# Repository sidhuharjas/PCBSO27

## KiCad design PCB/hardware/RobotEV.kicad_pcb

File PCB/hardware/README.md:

# EV Controller Board — Rev D (100% Through-Hole, Zero SMD)

Custom 2-layer carrier PCB for a **Science Olympiad Electric Vehicle (Division C, 2027)** built around a **Raspberry Pi Pico 2 (RP2350)**, an **8xAA battery pack**, a **Weka dual 20 A brushed ESC**, **two AS5600 magnetic wheel encoders**, a **WitMotion WT901 UART IMU**, and a **Waveshare 1.69" ST7789V2 IPS LCD**.

**Board geometry:** `85 × 65 mm`, 4 mm rounded corners, 4× M3 mounting holes on a `77 × 57 mm` pattern (100% drop-in chassis-compatible with Rev B/C).

---

## What Changed in Rev D (vs. Rev C)

| Metric / Feature | Rev C | **Rev D** | Improvement |
|---|---|---|---|
| **Soldered SMD components** | **26** | **0** | **100% through-hole — standard iron only** |
| **Electrical components to solder** | 29 | **12** | **59% fewer electrical parts** |
| **Total soldered parts (incl. connectors)** | 40 | **23** | **43% fewer solder joints** |
| **XT30 polarity (`J1` / `J2`)** | Reversed (`+` on GND!) | **Fixed (`Pin 1 = -`, `Pin 2 = +`)** | **Prevented dead short on plug-in** |
| **15 A main fuse (`F1`)** | Soldered 2920 SMD | **Keystone 3568 mini blade holder** | **Tool-free 2-second competition swap** |
| **15 A power bus copper** | Single-sided 3.0 mm | **Double-sided 3.0 mm (`F.Cu + B.Cu`)** | **2× copper cross-section (6 mm eff.)** |
| **3.3 V rail regulator** | External `AMS1117-3.3` + MLCC | **Pico 2 onboard `RT6154A` SMPS** | **Zero oscillation risk + USB-only bench testing** |
| **Hold-up cap `C14` rating** | 470 µF 16 V | **470 µF 25 V** | **Proper derating for 13.2 V fresh 8×AA** |
| **Routed signal/power vias** | 8 | **1** (0 on signals!) | **Cleaner 2-layer routing + solid GND planes** |

### Critical Bug Fixed from Rev C
- **Reversed XT30 polarity on `J1` and `J2`:** Official KiCad `AMASS_XT30PW-M` and `AMASS_XT30PW-F` footprints map **Pin 1 (square pad, `-` silk)** to negative and **Pin 2 (round pad, `+` silk)** to positive. Rev C wired Pin 1 to `VBAT`/`VBAT_F` and Pin 2 to `GND`, which would have dead-shorted the battery pack through `D4` and blown the fuse (or damaged the ESC) on first connection. Rev D corrects both connectors to `Pin 1 = GND (-)`, `Pin 2 = VBAT / VBAT_F (+)`, which also places `J1 (+)` and `J2 (+)` directly facing each other (`9.85 mm` apart) right beside the Keystone 3568 blade fuse holder (`9.92 mm` pitch).

### 17 Eliminated Components (Why Every Removal Makes the Board Better)
1. **`U3` (`AMS1117-3.3`) + `C13` + `C3` removed:** The Pico 2's built-in RT6154A buck-boost regulator (`Pin 36: 3V3`) is rated for **300 mA** external load. Total worst-case 3.3 V draw on this board is **≤128 mA** (LCD ≤90 mA + 2× AS5600 ~13 mA + WT901 <25 mA — >2.3× safety margin). Removing `U3` eliminates AMS1117's notorious low-ESR MLCC oscillation risk, eliminates back-powering hazards when plugged into USB, and lets you bench-test **the LCD, IMU, and encoders over USB alone without a battery**.
2. **`J6` (WT901 IMU) moved from `+5V` to `+3V3`:** The WT901 datasheet specifies `3.3–5 V` supply (`<25 mA`, `11.5 mA` typ.) and 3.3 V-only UART I/O. Running it on `+3V3` guarantees its UART stays powered in sync with the RP2350 on both battery and USB.
3. **`C12` (100 µF) removed:** Redundant with `C2` (`10 µF` low-ESR ceramic) and the Pico 2's onboard `47 µF` `VSYS` capacitor; keeps capacitive load well within RECOM `R-78E5.0-0.5`'s `≤100 µF` output-cap limit.
4. **`C5`, `C6`, `C7`, `C8` removed (kept shared `C4` 100 nF on east `+3V3` bus):** All four off-board breakouts (LCD, WT901, 2× AS5600) already carry their own onboard decoupling capacitors.
5. **`R3` (1 kΩ) removed:** The `100 kΩ / 22 kΩ` divider (`R1 || R2 = 18 kΩ`) already limits fault current into `GP26/ADC0` to `<0.2 mA` and forms an `88 Hz` low-pass filter directly with `C11` (`100 nF`).
6. **`R4`, `R5`, `C9`, `C10` removed:** The RP2350 has built-in programmable pull-ups (~50–80 kΩ) on `GP15`/`GP16` and handles button debounce in 5 lines of firmware.
7. **`D1`, `R6`, `D2`, `R7` removed:** Use the Pico 2's onboard `GP25` LED, the 1.69" IPS LCD, and test pads `TP1`–`TP4` for status and power verification (also frees `GP17` for future expansion).

---

## Power Architecture

```text
8xAA Pack (9.6–13.2 V)
  │
  ▼  J1 (XT30PW-M: Pin 1 '-' GND, Pin 2 '+' VBAT)
  ├──[ 3.0 mm F.Cu + 3.0 mm B.Cu bus ]──► F1 (Keystone 3568 + 15 A Mini Blade Fuse)
  │                                         │ VBAT_F
  │                                         ├──[ 3.0 mm F.Cu + 3.0 mm B.Cu ]──► J2 (XT30PW-F -> Weka Dual 20A ESC)
  │                                         ├──► D4 (P6KE18A 600 W TVS -> GND, clamps brushed-motor spikes)
  │                                         └──► J3 (Logic Power Switch, <250 mA)
  │                                                │ VBAT_SW (TP4)
  │                                                ▼
  │                                              D3 (1N5822 40V 3A Schottky: reverse-polarity + hold-up isolator)
  │                                                │ VBAT_D
  │                                                ├──► C14 (470 µF 25V hold-up) + C1 (10 µF 50V ceramic)
  │                                                ├──► R1 (100k) / R2 (22k) + C11 (100nF) ──► Pico GP26/ADC0
  │                                                └──► U2 (RECOM R-78E5.0-0.5, 5 V 500 mA buck)
  │                                                       │ +5V (TP1) + C2 (10 µF 50V ceramic)
  │                                                       ▼
  │                                                     D5 (1N5822 40V 3A Schottky OR-ing diode)
  │                                                       │ VSYS
  │                                                       ▼
  │                                              U1 (Raspberry Pi Pico 2, Pin 39 VSYS — USB-safe!)
  │                                                       │ Pin 36: +3V3 (onboard RT6154A SMPS, 300 mA max)
  │                                                       └──► C4 (100nF), TP2, J4 (ENC_L), J5 (ENC_R), J6 (WT901), J7 (LCD)
```

### Battery Voltage Sense Math (`GP26 / ADC0`)
- Divider ratio: `V_ADC = VBAT_D × 22k / (100k + 22k) = VBAT_D × 0.18033`
- Account for ~0.30 V drop across `D3` (`1N5822` at ~150 mA):
  `V_BATT ≈ (V_ADC / 0.18033) + 0.30 V`
- Fresh 8×AA alkaline (`13.2 V` → `VBAT_D ≈ 12.9 V`): `V_ADC = 2.33 V` (safe margin below `3.3 V` ADC max; survives up to `18.6 V` input!).

---

## RP2350 Pin Map (`U1` — Raspberry Pi Pico 2)

| Pico Pin | GPIO | Net | Destination | Firmware Notes |
|---|---|---|---|---|
| 1 | GP0 | `IMU_TX` | `J6.2` (WT901 RX) | UART0 TX (3.3 V logic) |
| 2 | GP1 | `IMU_RX` | `J6.3` (WT901 TX) | UART0 RX (3.3 V logic) |
| 4 | GP2 | `ESC_L` | `J10.1` | 50 Hz servo PWM (left motor) |
| 5 | GP3 | `ESC_R` | `J10.2` | 50 Hz servo PWM (right motor) |
| 6 | GP4 | `ENC_L_SDA` | `J4.3` | I2C0 SDA (AS5600 `0x36`, breakout has 4.7k pull-up) |
| 7 | GP5 | `ENC_L_SCL` | `J4.4` | I2C0 SCL |
| 9 | GP6 | `ENC_R_SDA` | `J5.3` | I2C1 SDA (AS5600 `0x36`, breakout has 4.7k pull-up) |
| 10 | GP7 | `ENC_R_SCL` | `J5.4` | I2C1 SCL |
| 12 | GP9 | `LCD_CS` | `J7.5` | SPI1 CS |
| 14 | GP10 | `LCD_SCK` | `J7.4` | SPI1 SCK |
| 15 | GP11 | `LCD_MOSI` | `J7.3` | SPI1 TX |
| 16 | GP12 | `LCD_DC` | `J7.6` | LCD Data/Command |
| 17 | GP13 | `LCD_RST` | `J7.7` | LCD Reset |
| 19 | GP14 | `LCD_BL` | `J7.8` | LCD Backlight (PWM dimmable) |
| 20 | GP15 | `BTN_START` | `J8.1` | **Enable internal pull-up** + 20 ms software debounce |
| 21 | GP16 | `BTN_MODE` | `J9.1` | **Enable internal pull-up** + 20 ms software debounce |
| 22 | GP17 | *(spare)* | — | Freed in Rev D (use Pico onboard `GP25` LED for status) |
| 31 | GP26 | `VBAT_ADC` | `R1`/`R2`/`C11` | ADC0 battery monitor (`88 Hz` LPF) |
| 36 | 3V3 | `+3V3` | `J4, J5, J6, J7, C4, TP2` | Onboard RT6154A SMPS output (≤128 mA / 300 mA max) |
| 39 | VSYS | `VSYS` | `D5.1 (K)` | OR-ed 5 V rail (~4.7 V after D5; USB-safe) |
| 3,8,13,18,23,28,33,38 | GND | `GND` | Solid top + bottom pours | Connected to 85 stitching vias |

---

## Connector Pinouts (Pin 1 = Square Pad on PCB)

| Ref | Label | Connector | Pinout |
|---|---|---|---|
| `J1` | `BATT 8xAA` | `AMASS XT30PW-M` | `1 = GND (-)` · `2 = VBAT (+)` |
| `J2` | `ESC PWR` | `AMASS XT30PW-F` | `1 = GND (-)` · `2 = VBAT_F (+)` |
| `J3` | `PWR SW` | `1×2 2.54 mm` header | `1 = VBAT_F` · `2 = VBAT_SW` |
| `J4` | `ENC L` | `JST-PH 4-pin` (2.0 mm) | `1 = +3V3` · `2 = GND` · `3 = SDA (GP4)` · `4 = SCL (GP5)` |
| `J5` | `ENC R` | `JST-PH 4-pin` (2.0 mm) | `1 = +3V3` · `2 = GND` · `3 = SDA (GP6)` · `4 = SCL (GP7)` |
| `J6` | `WT901` | `JST-PH 4-pin` (2.0 mm) | `1 = +3V3` · `2 = IMU_TX (→WT901 RX)` · `3 = IMU_RX (←WT901 TX)` · `4 = GND` |
| `J7` | `LCD` | `2×4 2.54 mm` header | Odd: `1=+3V3, 3=MOSI, 5=CS, 7=RST` · Even: `2=GND, 4=SCK, 6=DC, 8=BL` |
| `J8` | `START` | `JST-XH 2-pin` (2.5 mm) | `1 = BTN_START (GP15)` · `2 = GND` |
| `J9` | `MODE` | `JST-XH 2-pin` (2.5 mm) | `1 = BTN_MODE (GP16)` · `2 = GND` |
| `J10` | `ESC SIG` | `1×3 2.54 mm` header | `1 = ESC_L (GP2)` · `2 = ESC_R (GP3)` · `3 = GND` *(do NOT connect ESC BEC +5V)* |

---

## Complete PCB BOM (100% Through-Hole — 0 SMD, 23 Soldered Parts)

See `hardware/BOM.xlsx` for clickable vendor/cost rollups and off-board parts.

### 12 Electrical Components (9 Unique Part Types)
| Ref(s) | Qty | Value | Package / Footprint | Example Part Number |
|---|---|---|---|---|
| `F1` | 1 | 15 A Mini Blade | `Fuseholder_Blade_Mini_Keystone_3568` | Keystone `3568` + Littelfuse `0297015.WXNV` |
| `D4` | 1 | `P6KE18A` TVS | `D_DO-15_P10.16mm_Horizontal` | Littelfuse `P6KE18A` |
| `D3, D5` | 2 | `1N5822` 40V 3A | `D_DO-201AD_P12.70mm_Horizontal` | ON Semi / Vishay `1N5822` |
| `C14` | 1 | `470 µF 25 V` | `CP_Radial_D8.0mm_P3.50mm` | Nichicon `UPW1E471MPD` |
| `C1, C2` | 2 | `10 µF 50 V` X7R/S | `C_Disc_D6.0mm_W4.4mm_P5.00mm` | TDK `FG20X7R1H106KRT00` / Murata `RDEC71H106K3K1H03B` |
| `U2` | 1 | `R-78E5.0-0.5` | `Converter_DCDC_RECOM_R-78E-0.5_THT` | RECOM `R-78E5.0-0.5` |
| `C4, C11` | 2 | `100 nF 50 V` X7R | `C_Disc_D5.0mm_W2.5mm_P5.00mm` | KEMET `C320C104K5R5TA` |
| `R1` | 1 | `100 kΩ 1%` 1/4 W | `R_Axial_DIN0207_L6.3mm_D2.5mm_P10.16mm` | Yageo `MFR-25FBF52-100K` |
| `R2` | 1 | `22 kΩ 1%` 1/4 W | `R_Axial_DIN0207_L6.3mm_D2.5mm_P10.16mm` | Yageo `MFR-25FBF52-22K` |

### 11 Connectors & Sockets (All THT)
- `U1`: 2× 1×20 female 2.54 mm headers (Pico 2 socket)
- `J1`: AMASS `XT30PW-M` · `J2`: AMASS `XT30PW-F`
- `J4, J5, J6`: 3× JST `B4B-PH-K-S` (4-pin JST-PH)
- `J8, J9`: 2× JST `B2B-XH-A` (2-pin JST-XH)
- `J3`: 1×2 2.54 mm male header · `J10`: 1×3 2.54 mm male header · `J7`: 2×4 2.54 mm male header

---

## Soldering & Bring-Up Checklist (Shortest-to-Tallest Order)

1. **Solder lowest parts first:** `R1`, `R2`, `D4` (`K` band to square pad / `VBAT_F`), `D3` (`K` band to square pad / west), `D5` (`K` band to square pad / east).
2. **Ceramic caps:** `C1`, `C2`, `C4`, `C11` (non-polarized).
3. **Headers & sockets:** `J3`, `J7`, `J10`, `J4`–`J6`, `J8`–`J9`, and `U1` (plug a spare Pico 2 into the two 1×20 female strips temporarily while tacking the corner pins so the sockets stay dead parallel!).
4. **Tall & heavy power parts last:** `C14` (`+` long lead into square pad on west), `U2` (Pin 1 into square pad on west), `F1` (`Keystone 3568` — solder all 4 legs generously), `J1` (`XT30PW-M`), `J2` (`XT30PW-F`).
5. **Pre-power continuity check (NO Pico, NO battery, NO fuse):**
   - Check resistance `GND` ↔ `VBAT`, `GND` ↔ `VBAT_F`, `GND` ↔ `+5V`, `GND` ↔ `+3V3` — none should read dead short (`<10 Ω`).
   - Verify battery pack XT30-F polarity with a multimeter (`+` on rounded side, `-` on flat/beveled side).
6. **Power-up test (NO Pico plugged in yet):**
   - Insert 15 A mini blade fuse into `F1`, plug in 8×AA battery, close `J3` power switch.
   - Probe `TP4 (VSW)` → ~9.6–13.2 V; probe `TP1 (+5V)` vs `TP3 (GND)` → `5.0 V ± 0.1 V`; probe `U1` Pin 39 (`VSYS`) → `~4.65–4.75 V`.
7. **Install Pico 2** (USB port facing the south board edge as marked `USB`), plug in USB or turn on battery, and verify `TP2 (+3V3)` = `3.30 V ± 0.05 V`.

---

## Regenerating Files / Preparing Fab Gerbers

- Edit `tools/design.py` or `tools/placement.py`, then run:
  ```bash
  python tools/gen_sch.py     # regenerates hardware/RobotEV.kicad_sch
  python tools/relayout.py    # syncs footprints, places, routes, stitches GND, checks DRC
  python tools/make_bom.py    # regenerates hardware/BOM.xlsx
  python tools/render.py      # renders build/ & renders/ board_top.png + board_bottom.png
  ```
- **Before ordering PCBs:** Open `hardware/RobotEV.kicad_pcb` in **KiCad 10**, press **`B`** to fill the top & bottom GND copper pours, run **Inspect → Design Rules Checker**, and export Gerbers + Drill (or run `python tools/build.py` on a machine with KiCad 10 installed).
- Recommended fab settings: **2-layer, 1.6 mm FR-4, 1 oz Cu** (double-sided 3.0 mm `VBAT`/`VBAT_F` bars already deliver 6.0 mm effective copper width for 15 A peaks).

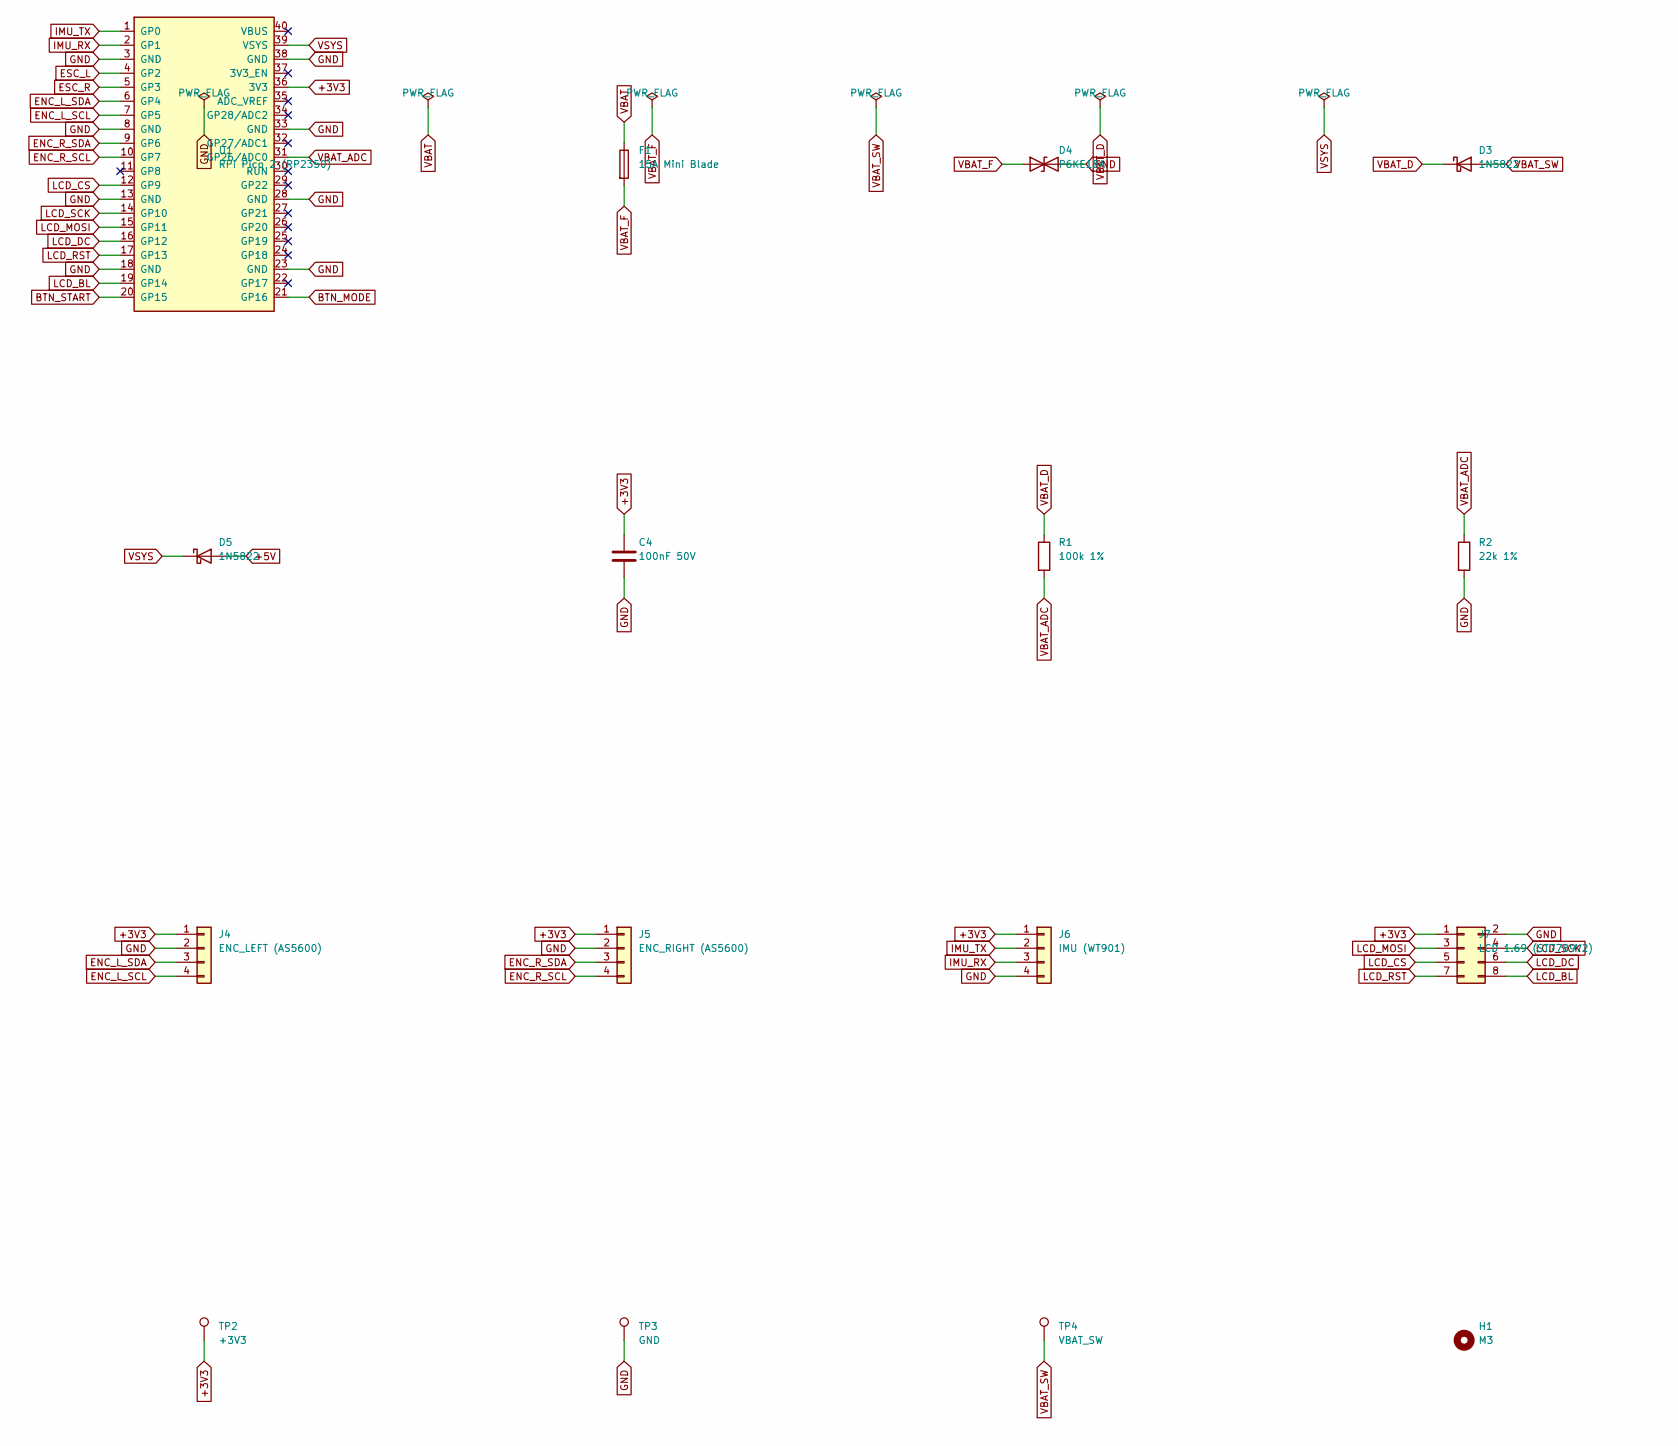
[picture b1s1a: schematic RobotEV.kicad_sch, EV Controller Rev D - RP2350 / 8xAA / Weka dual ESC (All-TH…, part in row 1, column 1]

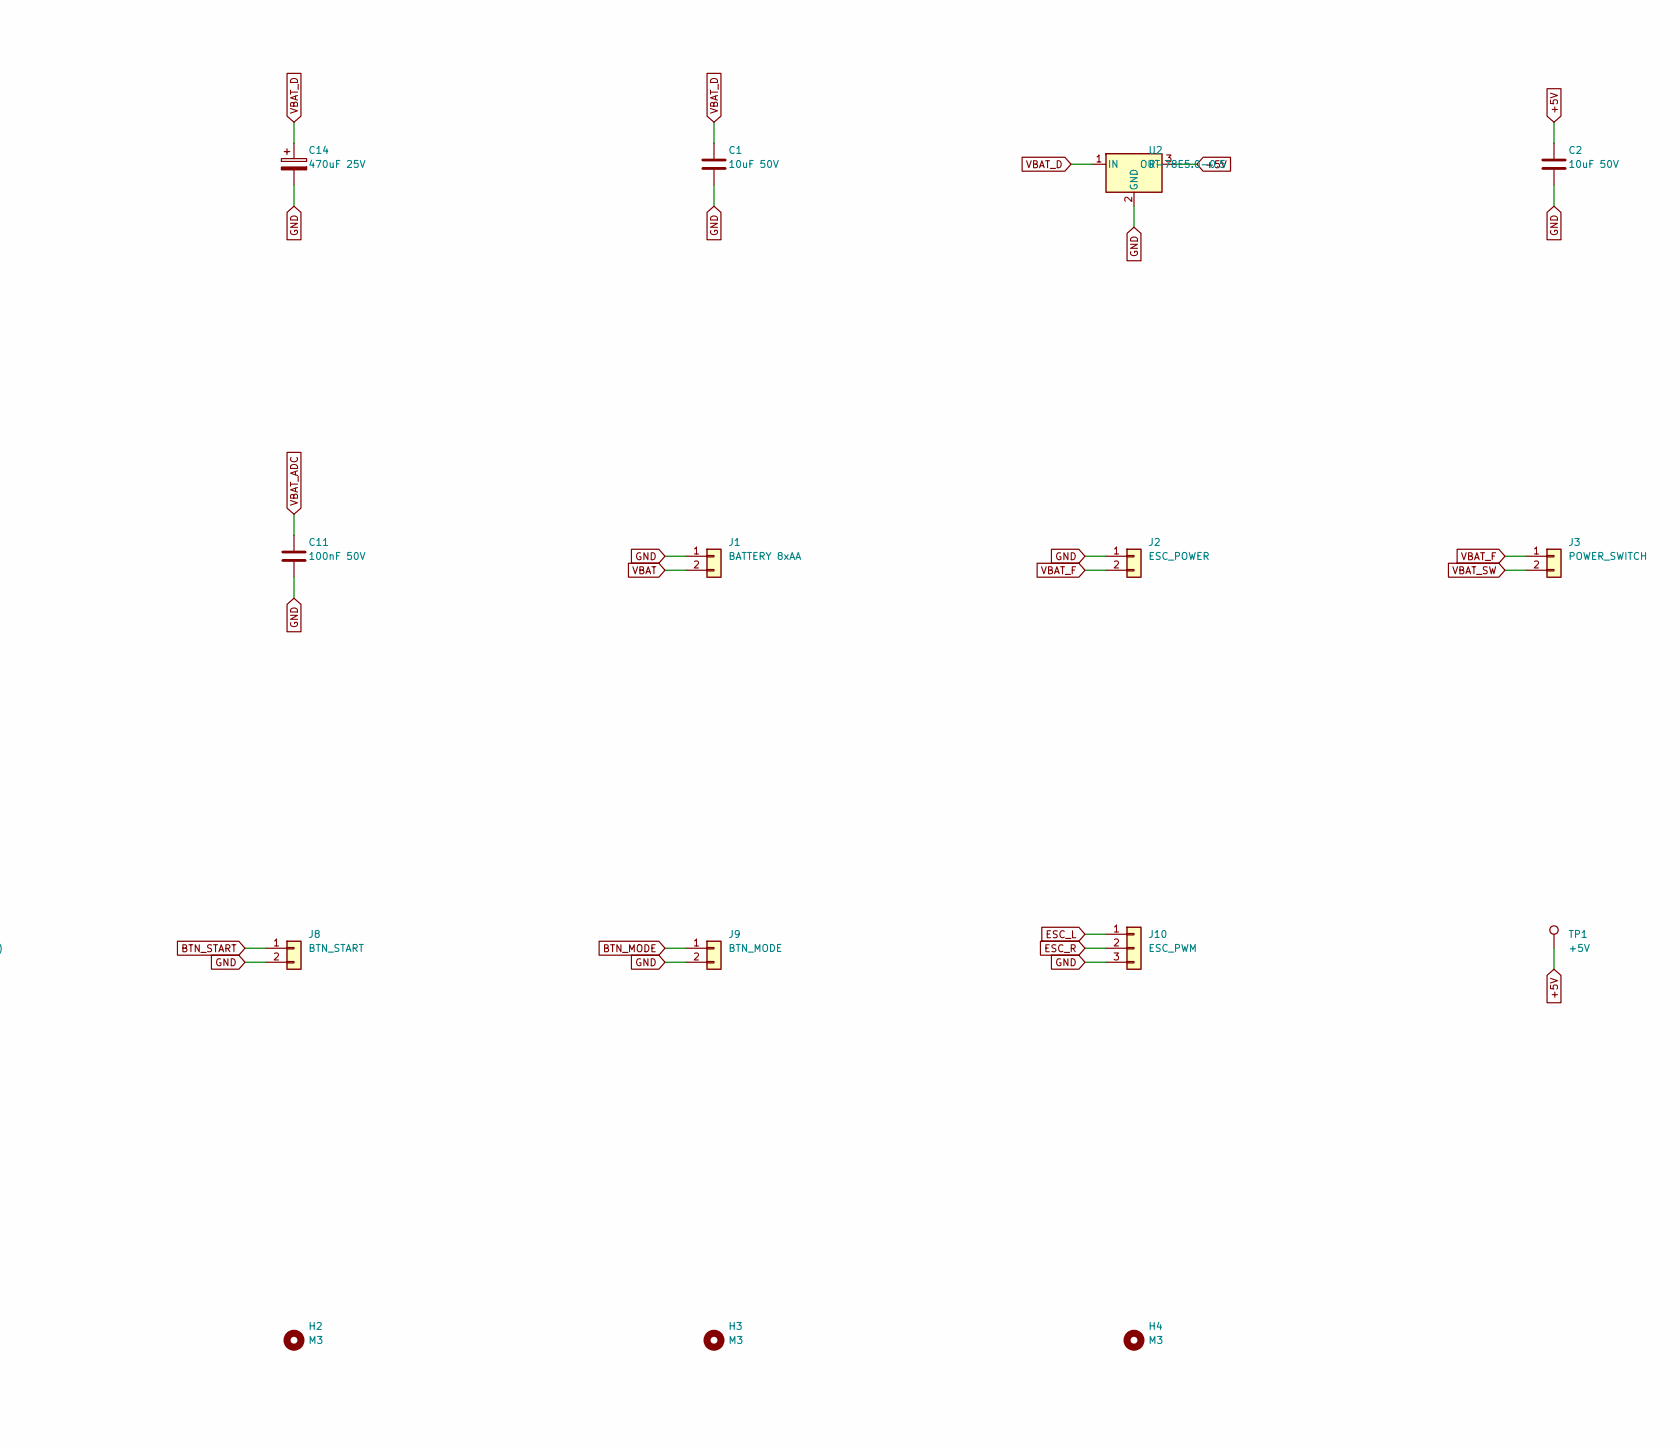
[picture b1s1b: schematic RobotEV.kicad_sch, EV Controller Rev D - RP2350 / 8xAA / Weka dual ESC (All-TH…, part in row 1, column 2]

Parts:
C1, C2: 10uF 50V; C_Disc_D6.0mm_W4.4mm_P5.00mm
C4, C11: 100nF 50V; C_Disc_D5.0mm_W2.5mm_P5.00mm
C14: 470uF 25V; CP_Radial_D8.0mm_P3.50mm
D3, D5: 1N5822; D_DO-201AD_P12.70mm_Horizontal
D4: P6KE18A; D_DO-15_P10.16mm_Horizontal
F1: 15A Mini Blade; Fuseholder_Blade_Mini_Keystone_3568
H1, H2, H3, H4: M3; MountingHole_3.2mm_M3
J1: BATTERY 8xAA; AMASS_XT30PW-M_1x02_P2.50mm_Horizontal
J2: ESC_POWER; AMASS_XT30PW-F_1x02_P2.50mm_Horizontal
J3: POWER_SWITCH; PinHeader_1x02_P2.54mm_Vertical
J4: ENC_LEFT (AS5600); JST_PH_B4B-PH-K_1x04_P2.00mm_Vertical
J5: ENC_RIGHT (AS5600); JST_PH_B4B-PH-K_1x04_P2.00mm_Vertical
J6: IMU (WT901); JST_PH_B4B-PH-K_1x04_P2.00mm_Vertical
J7: LCD 1.69 (ST7789V2); PinHeader_2x04_P2.54mm_Vertical
J8: BTN_START; JST_XH_B2B-XH-A_1x02_P2.50mm_Vertical
J9: BTN_MODE; JST_XH_B2B-XH-A_1x02_P2.50mm_Vertical
J10: ESC_PWM; PinHeader_1x03_P2.54mm_Vertical
R1: 100k 1%; R_Axial_DIN0207_L6.3mm_D2.5mm_P10.16mm_Horizontal
R2: 22k 1%; R_Axial_DIN0207_L6.3mm_D2.5mm_P10.16mm_Horizontal
TP1: +5V; TestPoint_Pad_D1.5mm
TP2: +3V3; TestPoint_Pad_D1.5mm
TP3: GND; TestPoint_Pad_D1.5mm
TP4: VBAT_SW; TestPoint_Pad_D1.5mm
U1: RPi Pico 2 (RP2350); Pico2_Socket_2x20_P2.54mm
U2: R-78E5.0-0.5; Converter_DCDC_RECOM_R-78E-0.5_THT

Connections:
+3V3: C4.1, J4.1, J5.1, J6.1, J7.1, TP2.1, U1.36 (3V3)
+5V: C2.1, D5.2 (A), TP1.1, U2.3 (OUT)
BTN_MODE: J9.1, U1.21 (GP16)
BTN_START: J8.1, U1.20 (GP15)
ENC_L_SCL: J4.4, U1.7 (GP5)
ENC_L_SDA: J4.3, U1.6 (GP4)
ENC_R_SCL: J5.4, U1.10 (GP7)
ENC_R_SDA: J5.3, U1.9 (GP6)
ESC_L: J10.1, U1.4 (GP2)
ESC_R: J10.2, U1.5 (GP3)
GND: C1.2, C2.2, C4.2, C11.2, C14.2, D4.2 (A2), J1.1, J2.1, J4.2, J5.2, J6.4, J7.2, J8.2, J9.2, J10.3, R2.2, TP3.1, U1.3 (GND), U1.8 (GND), U1.13 (GND), U1.18 (GND), U1.23 (GND), U1.28 (GND), U1.33 (GND), U1.38 (GND), U2.2 (GND)
IMU_RX: J6.3, U1.2 (GP1)
IMU_TX: J6.2, U1.1 (GP0)
LCD_BL: J7.8, U1.19 (GP14)
LCD_CS: J7.5, U1.12 (GP9)
LCD_DC: J7.6, U1.16 (GP12)
LCD_MOSI: J7.3, U1.15 (GP11)
LCD_RST: J7.7, U1.17 (GP13)
LCD_SCK: J7.4, U1.14 (GP10)
VBAT: F1.1, J1.2
VBAT_ADC: C11.1, R1.2, R2.1, U1.31 (GP26/ADC0)
VBAT_D: C1.1, C14.1, D3.1 (K), R1.1, U2.1 (IN)
VBAT_F: D4.1 (A1), F1.2, J2.2, J3.1
VBAT_SW: D3.2 (A), J3.2, TP4.1
VSYS: D5.1 (K), U1.39 (VSYS)

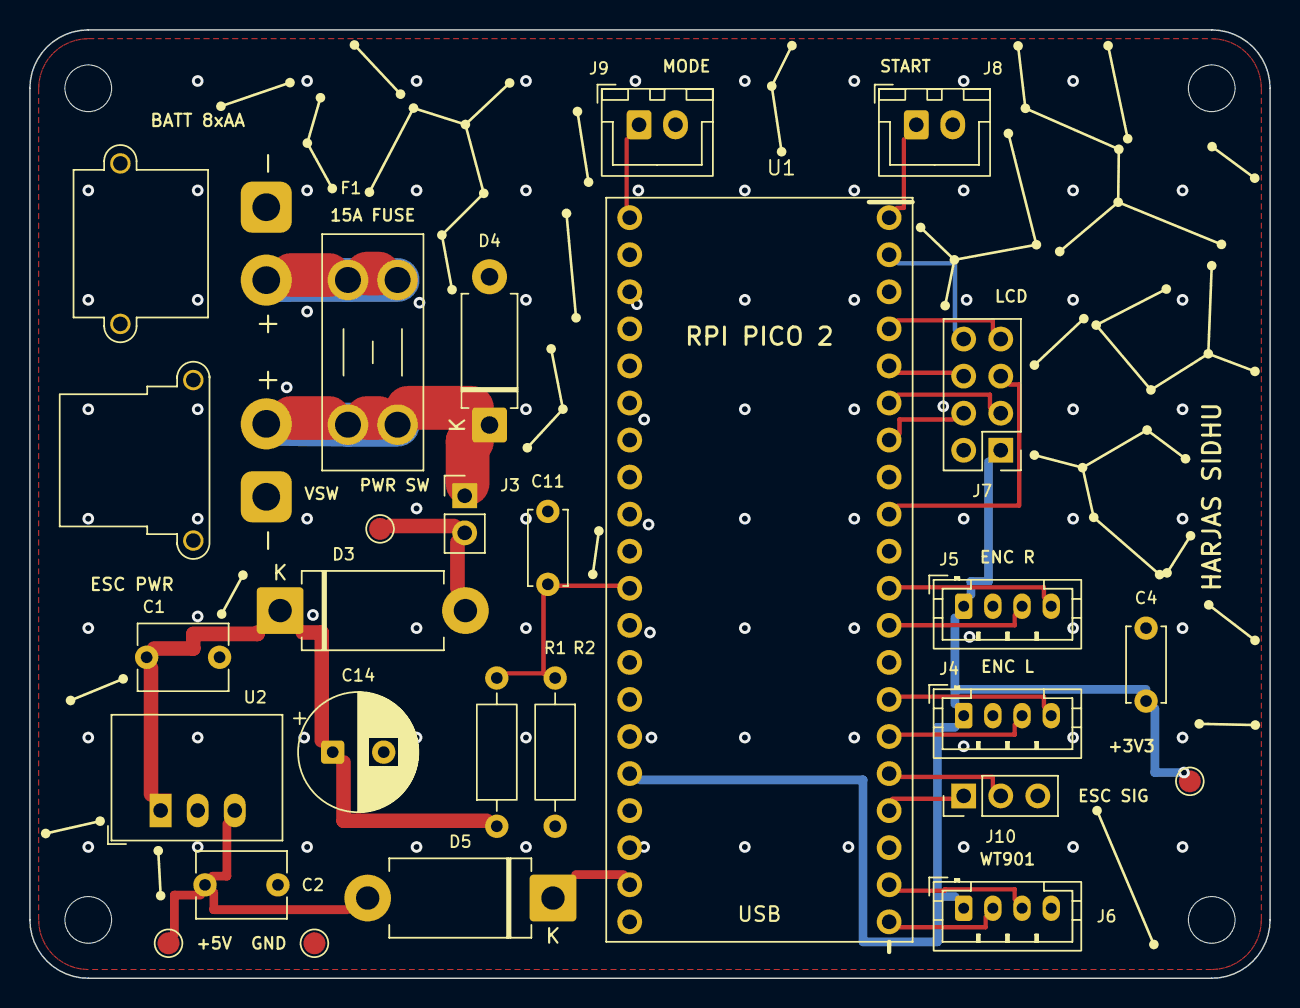
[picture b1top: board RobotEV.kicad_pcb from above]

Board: 2 copper layers, 85.0 x 65.0 mm, 31 parts (0 on the bottom side), 25 nets.

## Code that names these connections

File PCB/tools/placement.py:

"""Floorplan for Rev D (All-THT, Zero-SMD, 85 x 65 mm chassis-compatible).

(x, y, rot): footprint pad-bbox centre in mm (board top-left origin), KiCad rotation in degrees.
Board outline (85 x 65 mm, R=4 mm) and M3 holes (77 x 57 mm) match Rev B/C identically.
ZERO parts sit under the Pico 2 module.
"""
BOARD_W, BOARD_H, CORNER_R = 85.0, 65.0, 4.0
HOLES = [(4.0, 4.0), (81.0, 4.0), (4.0, 61.0), (81.0, 61.0)]   # M3, 77 x 57 mm pattern

# Every soldered component is through-hole and stays outside the Pico 2 outline
TALL = ['J1', 'J2', 'J3', 'J4', 'J5', 'J6', 'J7', 'J8', 'J9', 'J10',
        'F1', 'D3', 'D4', 'D5', 'U2', 'C1', 'C2', 'C4', 'C11', 'C14', 'R1', 'R2']

PICO_CX, PICO_CY = 50.0, 37.0   # Pico 2 sockets, rot 180 -> GP0-GP15 face east connectors, USB at south edge

# XT30 housings are placed by footprint origin (pad 1 = '-' GND); plug in from west edge.
# With fixed polarity: J1.2 (+ VBAT) is at (16.2, 17.15) and J2.2 (+ VBAT_F) is at (16.2, 27.00),
# facing each other 9.85 mm apart — matching Keystone 3568's 9.92 mm fuse pitch!
ORIGIN = {'J1': (16.2, 12.15, 90), 'J2': (16.2, 32.0, 90)}

PLACE = {
    'U1': (PICO_CX, PICO_CY, 180),

    # ---- High-current battery/ESC bus (west-north): straight 3.0 mm bars J1(+) -> F1 -> J2(+)
    'F1':  (23.5, 22.1, 270),    # Pad 1 pair at y=17.14 (level w/ J1+), Pad 2 pair at y=27.06 (level w/ J2+)
    'D4':  (31.5, 22.0, 90),     # P6KE18A TVS: K (VBAT_F) at y=27.08, A (GND) at y=16.92
    'J3':  (29.8, 33.2, 0),      # Power switch: Pin 1 (VBAT_F) top, Pin 2 (VBAT_SW) bottom

    # ---- Logic power chain (west-south): D3 -> C14/C1 -> U2 -> C2 -> D5 -> Pico VSYS
    'D3':  (23.5, 39.8, 0),      # 1N5822: A (VBAT_SW) east at x=29.85, K (VBAT_D) west at x=17.15
    'C1':  (10.5, 43.0, 0),      # 10 uF ceramic input bypass next to U2.1
    'C14': (22.5, 49.5, 0),      # 470 uF 25V hold-up electrolytic behind D3
    'U2':  (11.5, 53.5, 0),      # RECOM R-78E5.0-0.5 (Pin 1=VBAT_D, 2=GND, 3=+5V)
    'C2':  (14.5, 58.6, 0),      # 10 uF ceramic 5V output bypass next to U2.3
    'D5':  (29.5, 59.5, 180),    # 1N5822 OR-ing: A (+5V) west at x=23.15, K (VSYS) east at x=35.85 -> U1.39

    # ---- Battery voltage sense right beside Pico Pin 31 (GP26/ADC0 at 41.11, 38.27)
    'R1':  (32.0, 49.5, 90),     # 100k: Pin 1 (VBAT_D) bottom (54.58), Pin 2 (VBAT_ADC) top (44.42)
    'R2':  (36.0, 49.5, 270),    # 22k: Pin 1 (VBAT_ADC) top (44.42), Pin 2 (GND) bottom (54.58)
    'C11': (35.5, 35.5, 90),     # 100nF ADC filter right beside U1.31

    # ---- East connector column (pad rows aligned 1-to-1 with Pico pins)
    'J7':  (65.27, 25.0, 180),   # 1.69" ST7789V2 LCD (2x4 header, Pin 1 bottom-right -> 0 vias!)
    'J5':  (67.0, 39.5, 0),      # Right AS5600 encoder (I2C1)
    'J4':  (67.0, 47.0, 0),      # Left AS5600 encoder (I2C0)
    'J10': (66.54, 52.5, 90),    # Weka dual ESC PWM (1x3 header)
    'J6':  (67.0, 60.2, 0),      # WitMotion WT901 IMU (UART0, +3V3)
    'C4':  (76.5, 43.5, 90),     # Shared +3V3 bypass cap for east connector bank

    # ---- North edge buttons (direct to Pico GP16 / GP15, internal pull-ups)
    'J9':  (43.0, 6.5, 0),       # MODE button
    'J8':  (62.0, 6.5, 0),       # START button

    # ---- Test points (clean bottom-west / top-west probing pads)
    'TP1': (9.5, 62.6, 0),       # +5V
    'TP3': (19.5, 62.6, 0),      # GND
    'TP4': (24.0, 34.2, 0),      # VBAT_SW
    'TP2': (79.5, 51.5, 0),      # +3V3
}
PLACE.update({'H%d' % (i + 1): (x, y, 0) for i, (x, y) in enumerate(HOLES)})

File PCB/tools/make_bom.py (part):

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    ("ESC_POWER", "Connector_AMASS:AMASS_XT30PW-F_1x02_P2.50mm_Horizontal"):
        ("XT30PW-F right-angle PCB female socket (THT)", "AMASS",
         "XT30PW-F", "DigiKey / Amazon / AliExpress", 0.90,
         "Mates with male XT30 on Weka ESC; Pin 1 = '-' GND, Pin 2 = '+' VBAT_F"),
    ("POWER_SWITCH", "Connector_PinHeader_2.54mm:PinHeader_1x02_P2.54mm_Vertical"):
        ("2-pin 2.54 mm male header (THT)", "Molex / Amphenol",
         "22-28-4020 (or breakaway 1x40 strip)", "DigiKey", 0.25,
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    ("IMU (WT901)", "Connector_JST:JST_PH_B4B-PH-K_1x04_P2.00mm_Vertical"):
        ("JST-PH 4-pin 2.0 mm shrouded header (THT)", "JST",
         "B4B-PH-K-S", "DigiKey / Amazon", 0.35,
         "Pinout: 1=+3V3, 2=IMU_TX (to WT901 RX), 3=IMU_RX (from WT901 TX), 4=GND"),
    ("LCD 1.69 (ST7789V2)", "Connector_PinHeader_2.54mm:PinHeader_2x04_P2.54mm_Vertical"):
        ("2x4 (8-pin) 2.54 mm male pin header (THT)", "Amphenol / Sullins",
         "68001-108HLF", "DigiKey", 0.40,
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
